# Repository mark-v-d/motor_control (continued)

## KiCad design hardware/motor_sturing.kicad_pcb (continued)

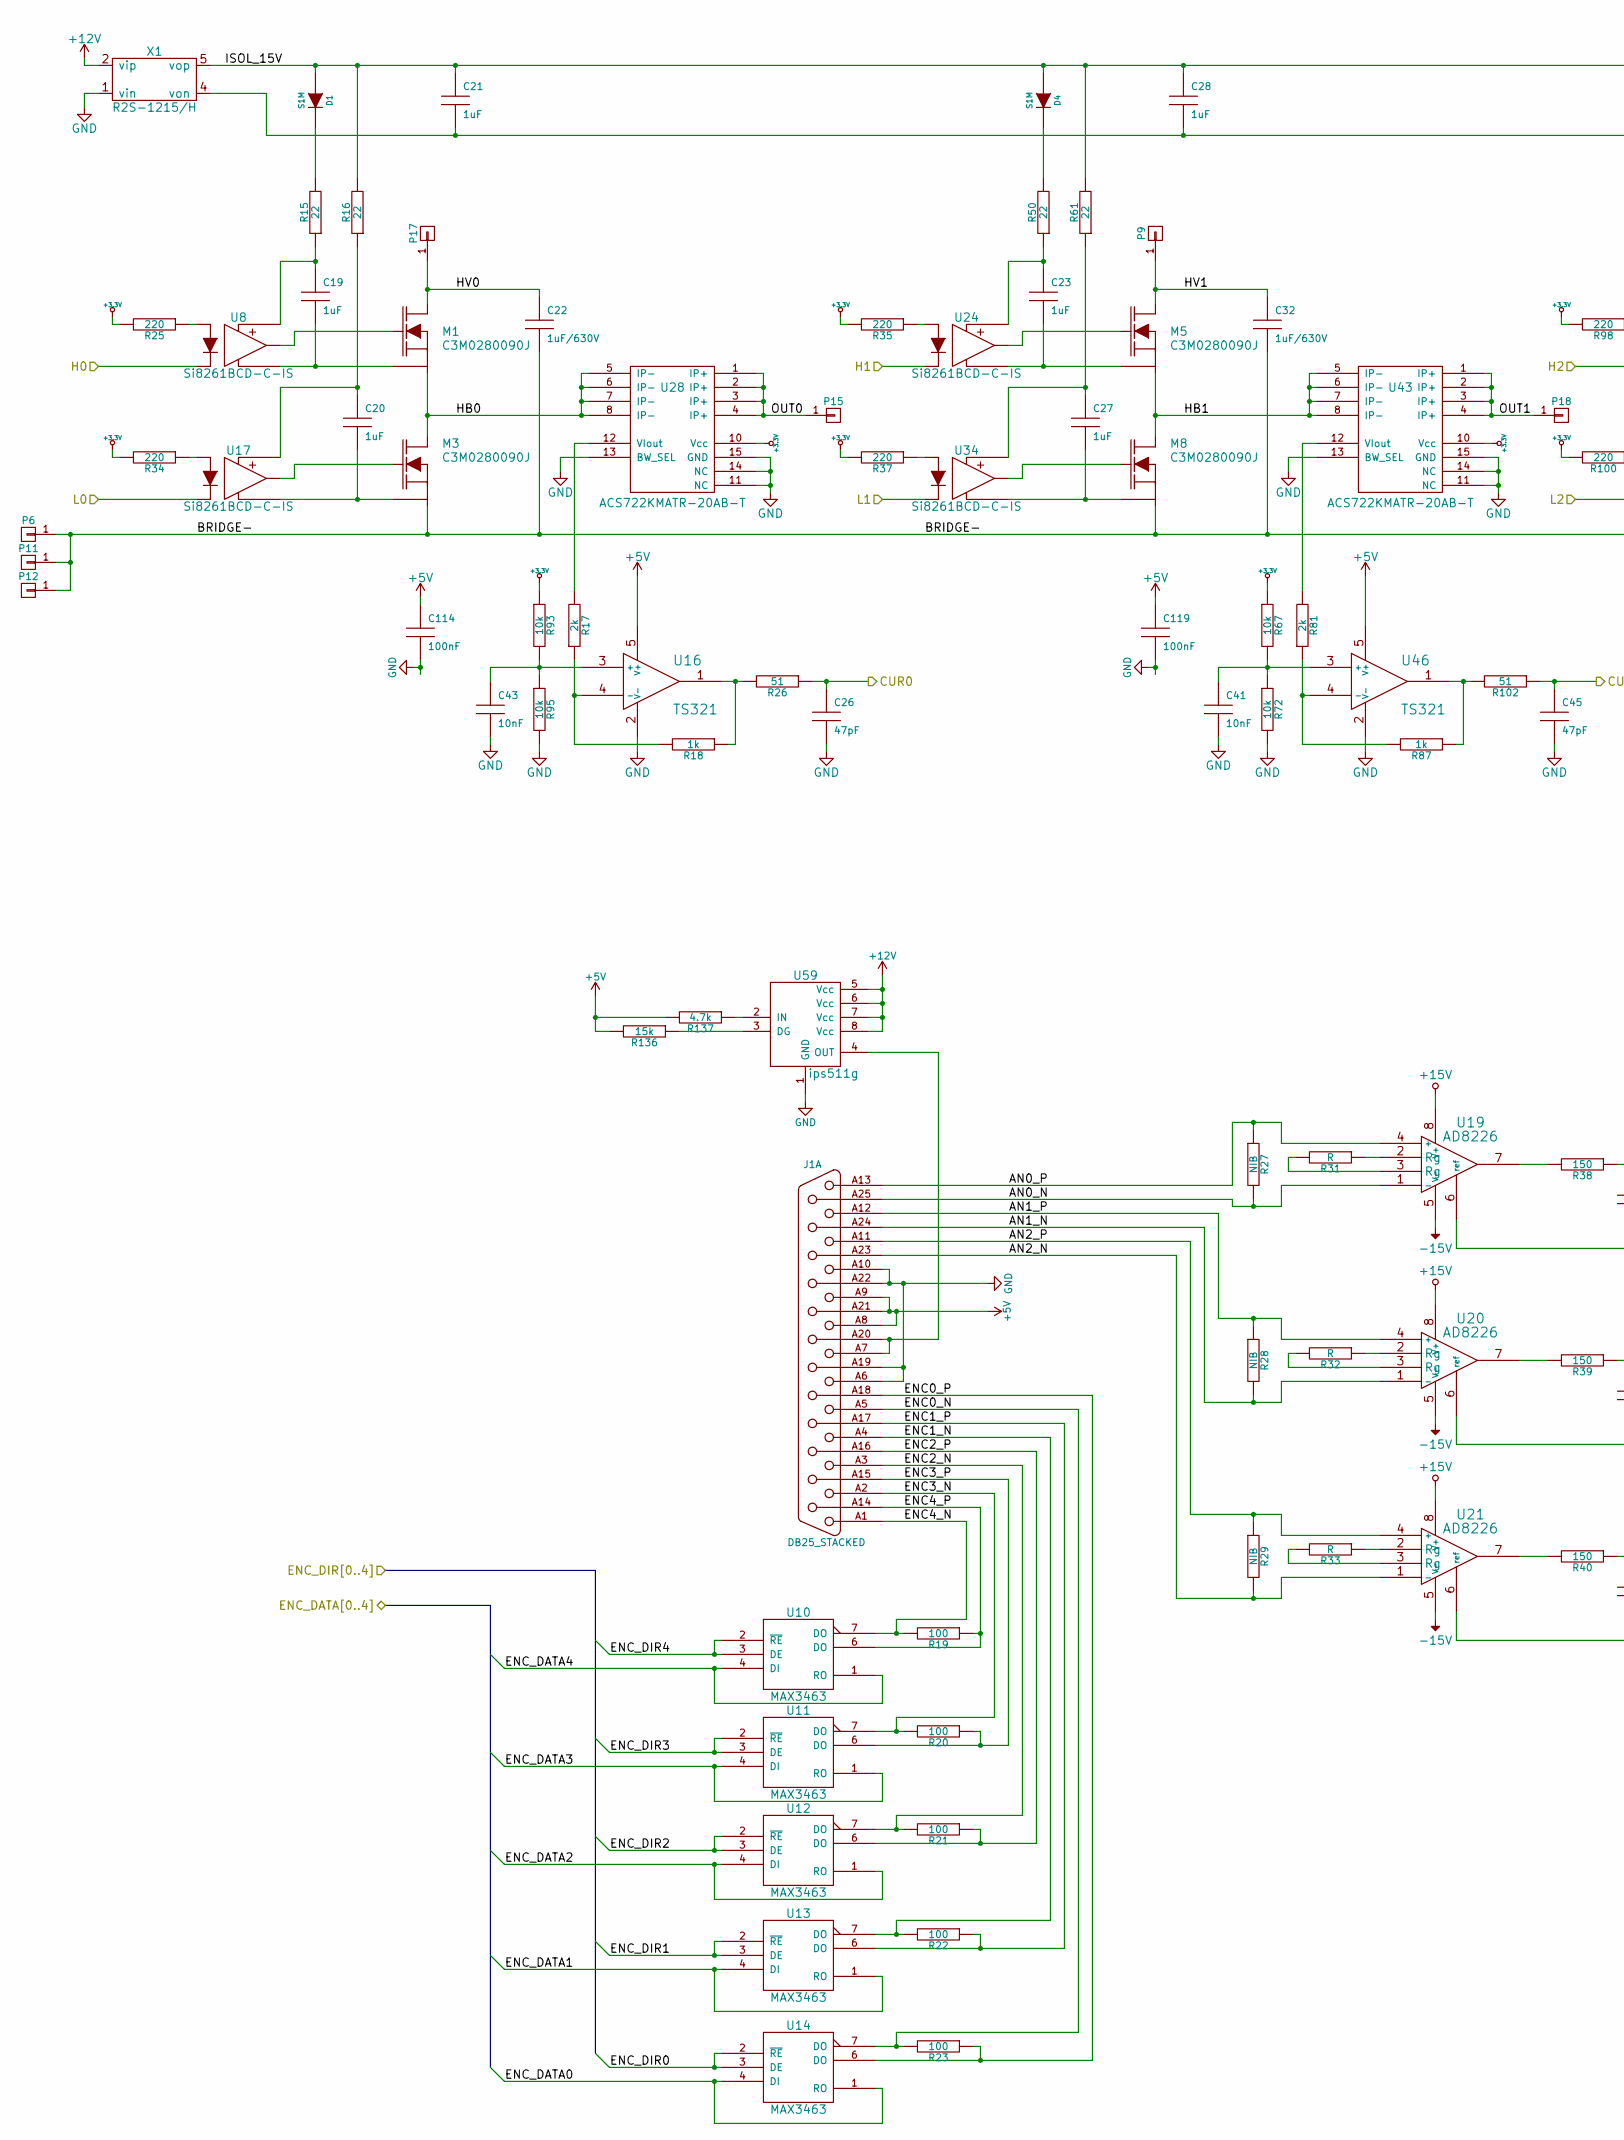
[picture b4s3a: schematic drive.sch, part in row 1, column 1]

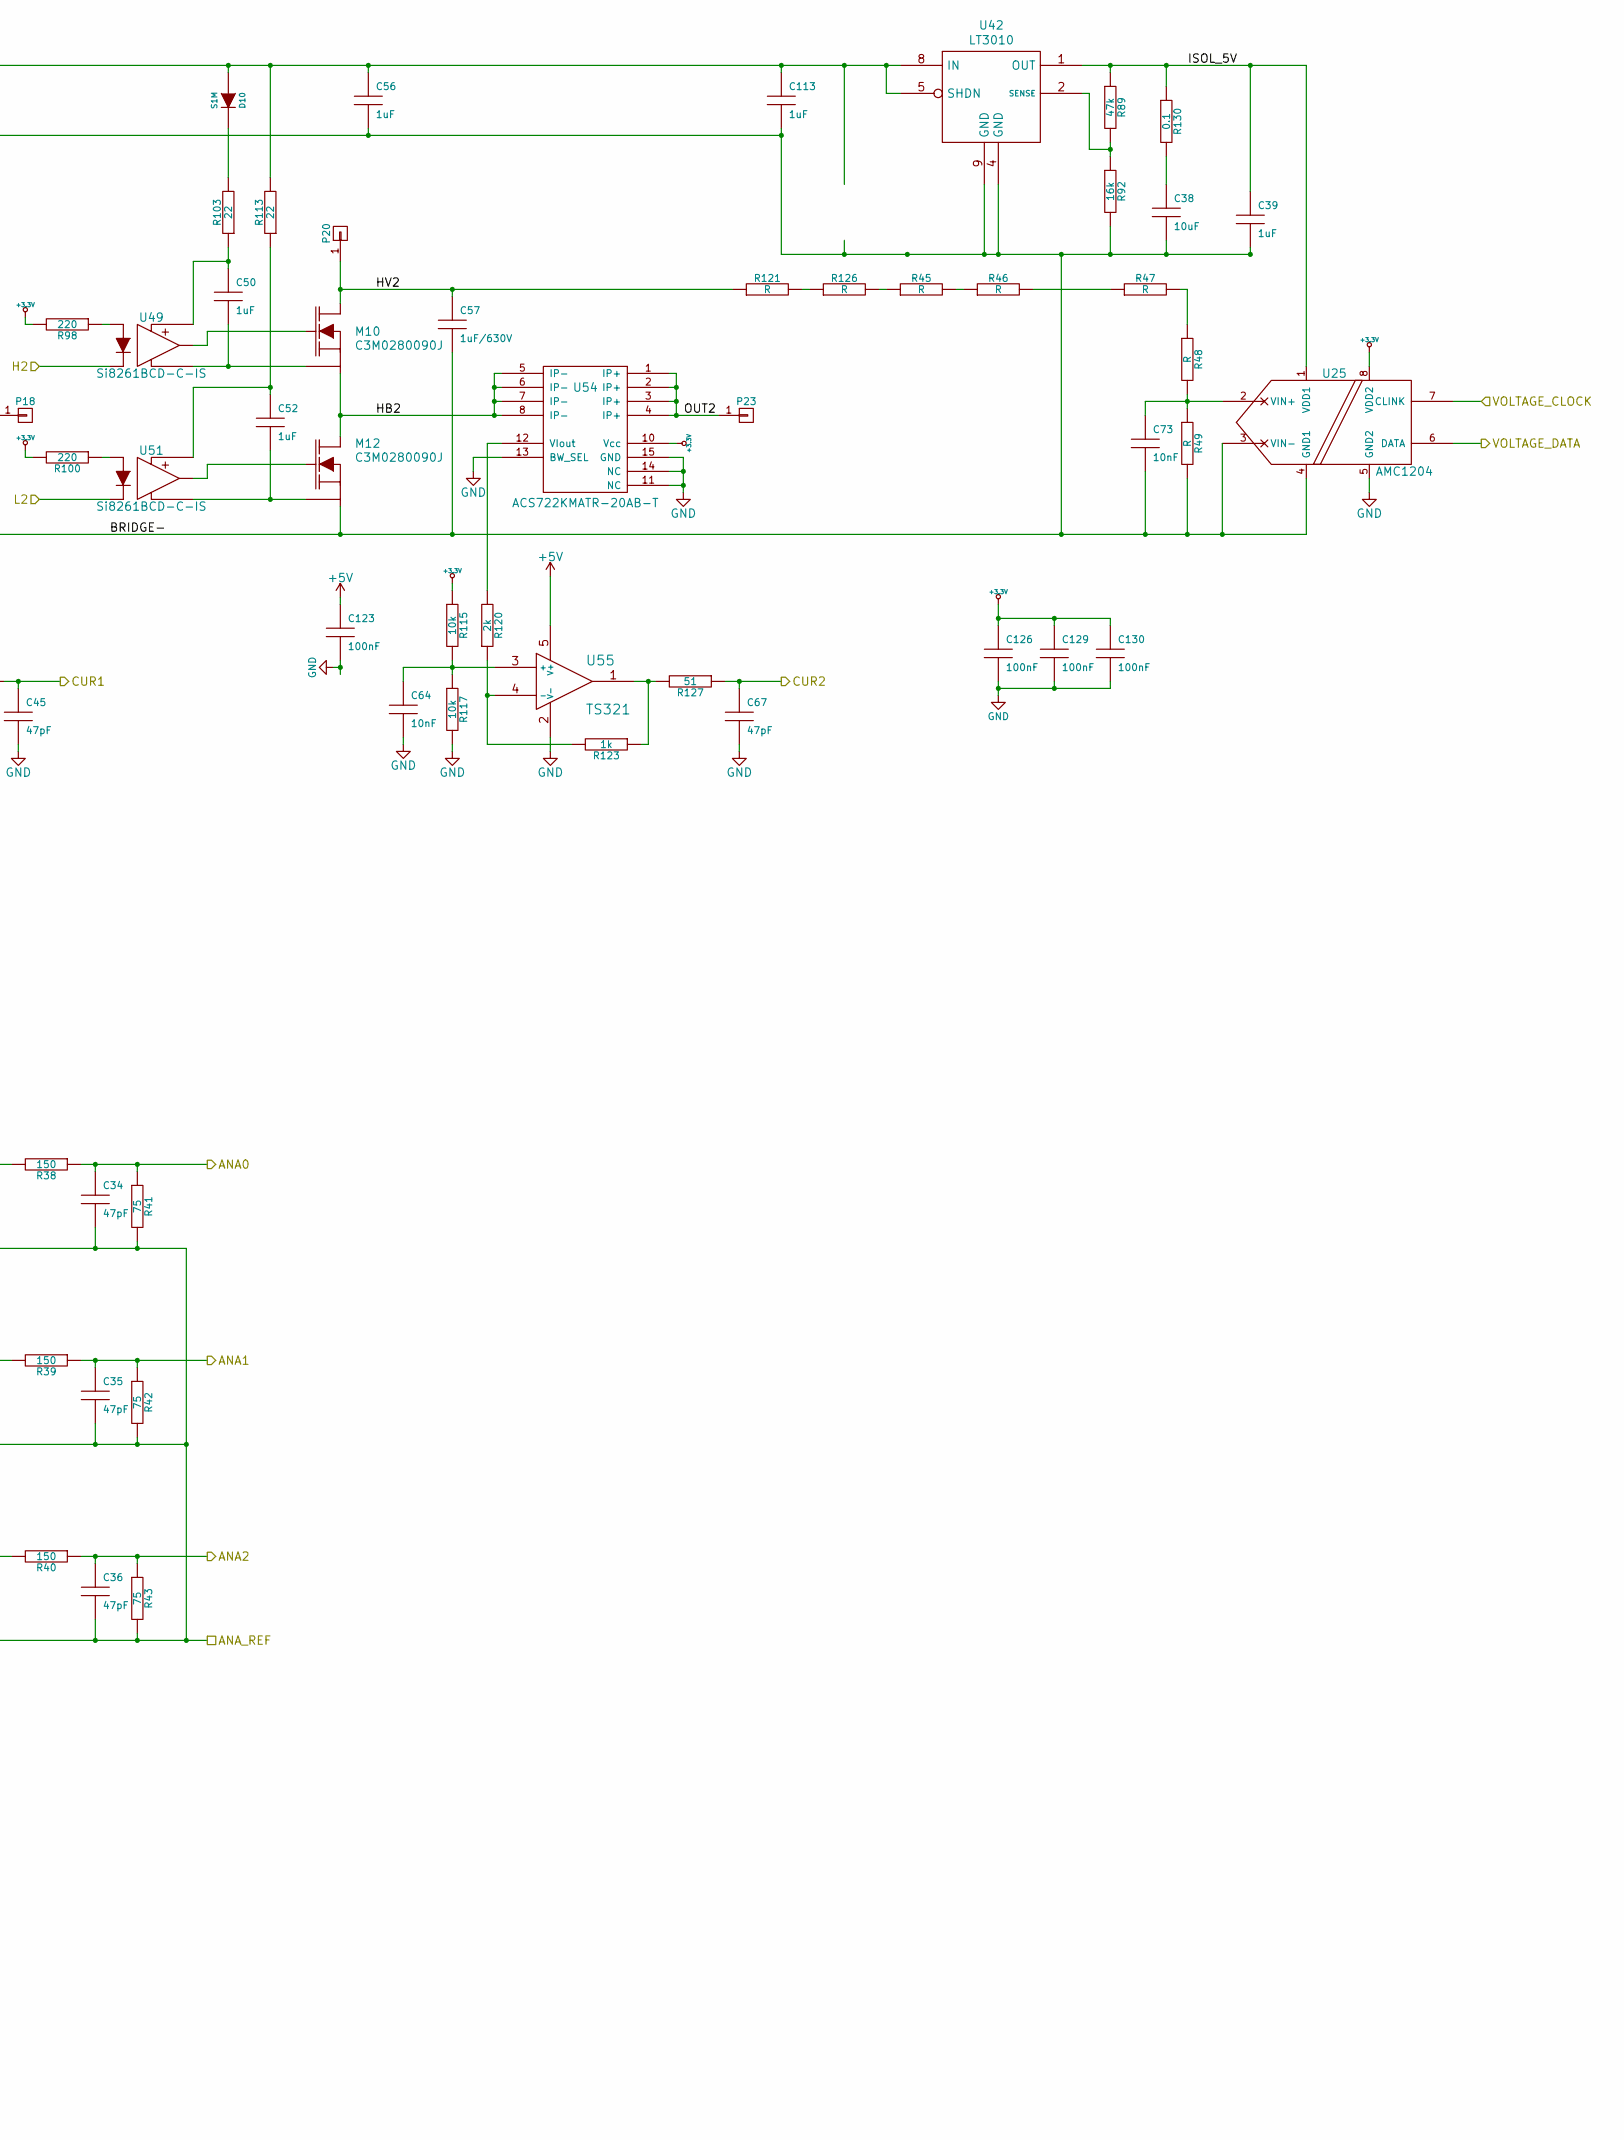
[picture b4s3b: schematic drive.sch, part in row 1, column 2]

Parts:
C19, C20, C21, C23, C27, C28, C39, C50, C52, C56, C113: 1uF; C0805
C22, C32, C57: 1uF/630V; C_2220
C26, C34, C35, C36, C45, C67: 47pF; C0603
C41, C43, C64, C73: 10nF; C0603
C65: 10uF; C1210
C115, C119, C123, C127, C129, C130: 100nF; C0603
D1, D4, D10: S1M; DO-214AC(SMA); Farnell 1858603
J1: DB25_STACKED; DB25FF_STACKED
M1, M3, M5, M8, M10, M12: C3M0280090J; TO-263-7-GDSKS; Mouser 941-C3M0280090J
P6: CONN_01X01; WE_9774080151R; Farnell 2497613
P9, P11, P12, P15, P17, P18, P20, P23: CONN_01X01; WE_9774080151R
R15, R16, R50, R61, R103, R113: 22; R0603
R17, R81, R120: 2k; R0603
R18, R87, R123: 1k; R0603
R19, R20, R21, R22, R23: 100; R0603
R25, R34, R35, R37, R98, R100: 220; R0603
R26, R102, R127: 51; R0603
R27, R28, R29: NIB; C0603
R31, R32, R33, R45, R46, R47, R48, R49, R121, R126: R; R0603
R38, R39, R40: 150; R0603
R41, R42, R43: 75; R0603
R67, R72, R93, R95, R115, R117: 10k; R0603
R89: 47k; R0603
R92: 16k; R0603
R129: 0.1; R0603
R135: 15k; R0603
R138: 4.7k; R0603
U8, U17, U24, U34, U49, U51: Si8261BCD-C-IS; SOIC-6_6.8x4.6mm_Pitch1.27mm; PartNr SI8261BCD-C-IS; Digikey 336-2418-5-ND
U9, U43, U54: ACS722KMATR-20AB-T; SOIC-16_7.5x10.3mm_Pitch1.27mm; PartNr ACS722KMATR-20AB; Digikey 620-1739-1-ND
U10, U11, U12, U13, U14: MAX3463; SOIC-8_3.9x4.9mm_Pitch1.27mm
U16, U46, U55: TS321; SOT23_5; PartNr TS321AILT; Farnell 1750165
U19, U20, U21: AD8226; SOIC-8_3.9x4.9mm_Pitch1.27mm; Farnell 1827360
U25: AMC1204; SO8_11; Digikey 296-37186-1-ND
U42: LT3010; MSOP-8-1EP_3x3mm_Pitch0.65mm; PartNr LT3010EMS8E#PBF; Farnell 1273635
U58: ips511g; SOIC-8_3.9x4.9mm_Pitch1.27mm
X1: R2S-1215/H; RECOM_R2S; Digikey R2S-1215/H-ND

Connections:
+3.3V: C127.1, C129.1, C130.1, R25.2, R34.2, R35.2, R37.2, R67.1, R93.1, R98.2, R100.2, R115.1, U9.10 (Vcc), U10.8 (+3.3V), U11.8 (+3.3V), U12.8 (+3.3V), U13.8 (+3.3V), U14.8 (+3.3V), U25.8 (VDD2), U43.10 (Vcc), U54.10 (Vcc); also elsewhere on the board
+5V: C115.1, C119.1, C123.1, J1.A8 (8), J1.A9 (9), J1.A21 (21), J1.B8 (8), J1.B9 (9), J1.B21 (21), R135.2, R138.2, U16.5 (V+), U46.5 (V+), U55.5 (V+); also elsewhere on the board
+12V: U58.5 (Vcc), U58.6 (Vcc), U58.7 (Vcc), U58.8 (Vcc), X1.2 (vip); also elsewhere on the board
+15V: U19.8 (V+), U20.8 (V+), U21.8 (V+); also elsewhere on the board
-15V: U19.5 (V-), U20.5 (V-), U21.5 (V-); also elsewhere on the board
/Drive_1/AN0_N: J1.A25 (P25), R27.2, U19.1 (-)
/Drive_1/AN0_P: J1.A13 (13), R27.1, U19.4 (+)
/Drive_1/AN1_N: J1.A24, R28.2, U20.1 (-)
/Drive_1/AN1_P: J1.A12 (12), R28.1, U20.4 (+)
/Drive_1/AN2_N: J1.A23 (P23), R29.2, U21.1 (-)
/Drive_1/AN2_P: J1.A11 (11), R29.1, U21.4 (+)
/Drive_1/ANA0: C34.1, R38.1, R41.1; also elsewhere on the board
/Drive_1/ANA1: C35.1, R39.1, R42.1; also elsewhere on the board
/Drive_1/ANA2: C36.1, R40.1, R43.1; also elsewhere on the board
/Drive_1/ANA_REF: C34.2, C35.2, C36.2, R41.2, R42.2, R43.2, U19.6 (ref), U20.6 (ref), U21.6 (ref); also elsewhere on the board
/Drive_1/CUR0: C26.1, R26.1; also elsewhere on the board
/Drive_1/CUR1: C45.1, R102.1; also elsewhere on the board
/Drive_1/CUR2: C67.1, R127.1; also elsewhere on the board
/Drive_1/ENC0_N: J1.A5 (5), R23.2, U14.7 (DO)
/Drive_1/ENC0_P: J1.A18 (P18), R23.1, U14.6 (DO)
/Drive_1/ENC1_N: J1.A4 (4), R22.2, U13.7 (DO)
/Drive_1/ENC1_P: J1.A17 (17), R22.1, U13.6 (DO)
/Drive_1/ENC2_N: J1.A3 (3), R21.2, U12.7 (DO)
/Drive_1/ENC2_P: J1.A16, R21.1, U12.6 (DO)
/Drive_1/ENC3_N: J1.A2, R20.2, U11.7 (DO)
/Drive_1/ENC3_P: J1.A15 (P15), R20.1, U11.6 (DO)
/Drive_1/ENC4_N: J1.A1 (1), R19.2, U10.7 (DO)
/Drive_1/ENC4_P: J1.A14 (P14), R19.1, U10.6 (DO)
/Drive_1/ENC_DATA0: U14.1 (RO), U14.4 (DI); also elsewhere on the board
/Drive_1/ENC_DATA1: U13.1 (RO), U13.4 (DI); also elsewhere on the board
/Drive_1/ENC_DATA2: U12.1 (RO), U12.4 (DI); also elsewhere on the board
/Drive_1/ENC_DATA3: U11.1 (RO), U11.4 (DI); also elsewhere on the board
/Drive_1/ENC_DATA4: U10.1 (RO), U10.4 (DI); also elsewhere on the board
/Drive_1/ENC_DIR0: U14.2 (~RE), U14.3 (DE); also elsewhere on the board
/Drive_1/ENC_DIR1: U13.2 (~RE), U13.3 (DE); also elsewhere on the board
/Drive_1/ENC_DIR2: U12.2 (~RE), U12.3 (DE); also elsewhere on the board
/Drive_1/ENC_DIR3: U11.2 (~RE), U11.3 (DE); also elsewhere on the board
/Drive_1/ENC_DIR4: U10.2 (~RE), U10.3 (DE); also elsewhere on the board
/Drive_1/H0: U8.3 (cathode); also elsewhere on the board
/Drive_1/H1: U24.3 (cathode); also elsewhere on the board
/Drive_1/H2: U49.3 (cathode); also elsewhere on the board
/Drive_1/HB1: M5.S, M8.D, U43.5 (IP-), U43.6 (IP-), U43.7 (IP-), U43.8 (IP-)
/Drive_1/HB2: M10.S, M12.D, U54.5 (IP-), U54.6 (IP-), U54.7 (IP-), U54.8 (IP-)
/Drive_1/HV0: C22.1, M1.D, P17.1
/Drive_1/HV1: C32.1, M5.D, P9.1
/Drive_1/HV2: C57.1, M10.D, P20.1, R121.1
/Drive_1/ISOL_15V: C21.1, C28.1, C56.1, C113.1, D1.A, D4.A, D10.A, R16.2, R61.2, R113.2, U42.5 (SHDN), U42.8 (IN), X1.5 (vop)
/Drive_1/OUT1: P18.1, U43.1 (IP+), U43.2 (IP+), U43.3 (IP+), U43.4 (IP+)
/Drive_1/OUT2: P23.1, U54.1 (IP+), U54.2 (IP+), U54.3 (IP+), U54.4 (IP+)
/Drive_1/VOLTAGE_CLOCK: U25.7 (CLINK); also elsewhere on the board
/Drive_2/AN0_N: J1.B25 (P25); also elsewhere on the board
/Drive_2/AN0_P: J1.B13 (13); also elsewhere on the board
/Drive_2/AN1_N: J1.B24 (A24); also elsewhere on the board
/Drive_2/AN1_P: J1.B12 (12); also elsewhere on the board
/Drive_2/AN2_N: J1.B23 (P23); also elsewhere on the board
/Drive_2/AN2_P: J1.B11 (11); also elsewhere on the board
/Drive_2/ENC0_N: J1.B5 (5); also elsewhere on the board
/Drive_2/ENC0_P: J1.B18 (P18); also elsewhere on the board
/Drive_2/ENC1_N: J1.B4 (4); also elsewhere on the board
/Drive_2/ENC1_P: J1.B17 (17); also elsewhere on the board
/Drive_2/ENC2_N: J1.B3 (3); also elsewhere on the board
/Drive_2/ENC2_P: J1.B16 (A16); also elsewhere on the board
/Drive_2/ENC3_N: J1.B2 (A2); also elsewhere on the board
/Drive_2/ENC3_P: J1.B15 (P15); also elsewhere on the board
/Drive_2/ENC4_N: J1.B1 (1); also elsewhere on the board
/Drive_2/ENC4_P: J1.B14 (P14); also elsewhere on the board
/FPGA/HB_L0: U17.3 (cathode); also elsewhere on the board
/FPGA/HB_L1: U34.3 (cathode); also elsewhere on the board
/FPGA/HB_L2: U51.3 (cathode); also elsewhere on the board
/FPGA/VOLTAGE_D0: U25.6 (DATA); also elsewhere on the board
GND: C26.2, C41.2, C43.2, C45.2, C64.2, C67.2, C115.2, C119.2, C123.2, C127.2, C129.2, C130.2, J1.A6 (6), J1.A10 (10), J1.A19 (P19), J1.A22 (P22), J1.B6 (6), J1.B10 (10), J1.B19 (P19), J1.B22 (P22), R72.2, R95.2, R117.2, U9.11 (NC), U9.13 (BW_SEL), U9.14 (NC), U9.15 (GND), U10.5 (GND), U11.5 (GND), U12.5 (GND), U13.5 (GND), U14.5 (GND), U16.2 (V-), U25.5 (GND2), U43.11 (NC), U43.13 (BW_SEL), U43.14 (NC), U43.15 (GND), U46.2 (V-), U54.11 (NC), U54.13 (BW_SEL), U54.14 (NC), U54.15 (GND), U55.2 (V-), U58.1 (GND), X1.1 (vin); also elsewhere on the board
unnamed: C19.1, R15.1, U8.6 (vcc)
unnamed: C19.2, M1.KS (ks), U8.4 (gnd)
unnamed: C20.1, R16.1, U17.6 (vcc)
unnamed: C20.2, M3.KS (ks), U17.4 (gnd)
unnamed: C23.1, R50.1, U24.6 (vcc)
unnamed: C23.2, M5.KS (ks), U24.4 (gnd)
unnamed: C27.1, R61.1, U34.6 (vcc)
unnamed: C27.2, M8.KS (ks), U34.4 (gnd)
unnamed: C41.1, R67.2, R72.1, U46.3 (+)
unnamed: C43.1, R93.2, R95.1, U16.3 (+)
unnamed: C50.1, R103.1, U49.6 (vcc)
unnamed: C50.2, M10.KS (ks), U49.4 (gnd)
unnamed: C52.1, R113.1, U51.6 (vcc)
unnamed: C52.2, M12.KS (ks), U51.4 (gnd)
unnamed: C64.1, R115.2, R117.1, U55.3 (+)
unnamed: C65.1, R129.2
unnamed: C73.1, R48.2, R49.1, U25.2 (VIN+)
unnamed: D1.C, R15.2
unnamed: D4.C, R50.2
unnamed: D10.C, R103.2
unnamed: M1.G, U8.5 (out)
unnamed: M3.G, U17.5 (out)
unnamed: M5.G, U24.5 (out)
unnamed: M8.G, U34.5 (out)
unnamed: M10.G, U49.5 (out)
unnamed: M12.G, U51.5 (out)
unnamed: R17.1, R18.2, U16.4 (-)
unnamed: R18.1, R26.2, U16.1
unnamed: R25.1, U8.1 (anode)
unnamed: R31.1, U19.2 (Rg)
unnamed: R31.2, U19.3 (Rg)
unnamed: R32.1, U20.2 (Rg)
unnamed: R32.2, U20.3 (Rg)
unnamed: R33.1, U21.2 (Rg)
unnamed: R33.2, U21.3 (Rg)
unnamed: R34.1, U17.1 (anode)
unnamed: R35.1, U24.1 (anode)
unnamed: R37.1, U34.1 (anode)
unnamed: R38.2, U19.7
unnamed: R39.2, U20.7
unnamed: R40.2, U21.7
unnamed: R45.2, R46.1
unnamed: R46.2, R47.1
unnamed: R47.2, R48.1
unnamed: R81.1, R87.2, U46.4 (-)
unnamed: R81.2, U43.12 (VIout)
unnamed: R89.2, R92.1, U42.2 (SENSE)
unnamed: R98.1, U49.1 (anode)
unnamed: R100.1, U51.1 (anode)
unnamed: R87.1, R102.2, U46.1
unnamed: R120.1, R123.2, U55.4 (-)
unnamed: R120.2, U54.12 (VIout)
unnamed: R121.2, R126.1
unnamed: R123.1, R127.2, U55.1
unnamed: R45.1, R126.2
unnamed: R135.1, U58.3 (DG)
unnamed: R138.1, U58.2 (IN)

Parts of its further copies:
C24, C25, C29, C46, C47, C48, C51, C54, C55, C66, C112: 1uF; C0805
C30, C49, C58: 1uF/630V; C_2220
C37, C42, C59, C74: 10nF; C0603
C38: 10uF; C1210
C44, C53, C61, C62, C63, C68: 47pF; C0603
C114, C118, C122, C126, C128, C131: 100nF; C0603
D3, D7, D9: S1M; DO-214AC(SMA); Farnell 1858603
M2, M4, M6, M7, M9, M11: C3M0280090J; TO-263-7-GDSKS; Mouser 941-C3M0280090J
P7: CONN_01X01; WE_9774080151R; Farnell 2497613
P8, P10, P13, P14, P16, P19, P21, P22: CONN_01X01; WE_9774080151R
R24, R30, R36, R44, R97, R99: 220; R0603
R51, R52, R53, R62, R104, R114: 22; R0603
R54, R74, R119: 2k; R0603
R55, R88, R124: 1k; R0603
R56, R57, R58, R59, R60: 100; R0603
R63, R101, R128: 51; R0603
R64, R65, R66: NIB; C0603
R68, R69, R70, R82, R83, R84, R85, R86, R122, R125: R; R0603
R71, R73, R94, R96, R116, R118: 10k; R0603
R75, R76, R77: 150; R0603
R78, R79, R80: 75; R0603
R90: 47k; R0603
R91: 16k; R0603
R130: 0.1; R0603
R136: 15k; R0603
R137: 4.7k; R0603
U15, U18, U27, U35, U48, U52: Si8261BCD-C-IS; SOIC-6_6.8x4.6mm_Pitch1.27mm; PartNr SI8261BCD-C-IS; Digikey 336-2418-5-ND
U23: LT3010; MSOP-8-1EP_3x3mm_Pitch0.65mm; PartNr LT3010EMS8E#PBF; Farnell 1273635
U28, U36, U53: ACS722KMATR-20AB-T; SOIC-16_7.5x10.3mm_Pitch1.27mm; PartNr ACS722KMATR-20AB; Digikey 620-1739-1-ND
U29, U30, U31, U32, U33: MAX3463; SOIC-8_3.9x4.9mm_Pitch1.27mm
U37, U47, U56: TS321; SOT23_5; PartNr TS321AILT; Farnell 1750165
U38, U39, U40: AD8226; SOIC-8_3.9x4.9mm_Pitch1.27mm; Farnell 1827360
U44: AMC1204; SO8_11; Digikey 296-37186-1-ND
U59: ips511g; SOIC-8_3.9x4.9mm_Pitch1.27mm
X2: R2S-1215/H; RECOM_R2S; Digikey R2S-1215/H-ND

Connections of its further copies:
+3.3V: C126.1, C128.1, C131.1, R24.2, R30.2, R36.2, R44.2, R71.1, R94.1, R97.2, R99.2, R116.1, U28.10 (Vcc), U29.8 (+3.3V), U30.8 (+3.3V), U31.8 (+3.3V), U32.8 (+3.3V), U33.8 (+3.3V), U36.10 (Vcc), U44.8 (VDD2), U53.10 (Vcc); also elsewhere on the board
+5V: C114.1, C118.1, C122.1, R136.2, R137.2, U37.5 (V+), U47.5 (V+), U56.5 (V+); also elsewhere on the board
+12V: U59.5 (Vcc), U59.6 (Vcc), U59.7 (Vcc), U59.8 (Vcc), X2.2 (vip); also elsewhere on the board
+15V: U38.8 (V+), U39.8 (V+), U40.8 (V+); also elsewhere on the board
-15V: U38.5 (V-), U39.5 (V-), U40.5 (V-); also elsewhere on the board
/Drive_1/ANA_REF: C61.2, C62.2, C63.2, R78.2, R79.2, R80.2, U38.6 (ref), U39.6 (ref), U40.6 (ref); also elsewhere on the board
/Drive_1/VOLTAGE_CLOCK: U44.7 (CLINK); also elsewhere on the board
/Drive_2/AN0_N: R64.2, U38.1 (-); also elsewhere on the board
/Drive_2/AN0_P: R64.1, U38.4 (+); also elsewhere on the board
/Drive_2/AN1_N: R65.2, U39.1 (-); also elsewhere on the board
/Drive_2/AN1_P: R65.1, U39.4 (+); also elsewhere on the board
/Drive_2/AN2_N: R66.2, U40.1 (-); also elsewhere on the board
/Drive_2/AN2_P: R66.1, U40.4 (+); also elsewhere on the board
/Drive_2/ANA0: C61.1, R75.1, R78.1; also elsewhere on the board
/Drive_2/ANA1: C62.1, R76.1, R79.1; also elsewhere on the board
/Drive_2/ANA2: C63.1, R77.1, R80.1; also elsewhere on the board
/Drive_2/CUR0: C53.1, R63.1; also elsewhere on the board
/Drive_2/CUR1: C44.1, R101.1; also elsewhere on the board
/Drive_2/CUR2: C68.1, R128.1; also elsewhere on the board
/Drive_2/ENC0_N: R60.2, U33.7 (DO); also elsewhere on the board
/Drive_2/ENC0_P: R60.1, U33.6 (DO); also elsewhere on the board
/Drive_2/ENC1_N: R59.2, U32.7 (DO); also elsewhere on the board
/Drive_2/ENC1_P: R59.1, U32.6 (DO); also elsewhere on the board
/Drive_2/ENC2_N: R58.2, U31.7 (DO); also elsewhere on the board
/Drive_2/ENC2_P: R58.1, U31.6 (DO); also elsewhere on the board
/Drive_2/ENC3_N: R57.2, U30.7 (DO); also elsewhere on the board
/Drive_2/ENC3_P: R57.1, U30.6 (DO); also elsewhere on the board
/Drive_2/ENC4_N: R56.2, U29.7 (DO); also elsewhere on the board
/Drive_2/ENC4_P: R56.1, U29.6 (DO); also elsewhere on the board
/Drive_2/ENC_DATA0: U33.1 (RO), U33.4 (DI); also elsewhere on the board
/Drive_2/ENC_DATA1: U32.1 (RO), U32.4 (DI); also elsewhere on the board
/Drive_2/ENC_DATA2: U31.1 (RO), U31.4 (DI); also elsewhere on the board
/Drive_2/ENC_DATA3: U30.1 (RO), U30.4 (DI); also elsewhere on the board
/Drive_2/ENC_DATA4: U29.1 (RO), U29.4 (DI); also elsewhere on the board
/Drive_2/ENC_DIR0: U33.2 (~RE), U33.3 (DE); also elsewhere on the board
/Drive_2/ENC_DIR1: U32.2 (~RE), U32.3 (DE); also elsewhere on the board
/Drive_2/ENC_DIR2: U31.2 (~RE), U31.3 (DE); also elsewhere on the board
/Drive_2/ENC_DIR3: U30.2 (~RE), U30.3 (DE); also elsewhere on the board
/Drive_2/ENC_DIR4: U29.2 (~RE), U29.3 (DE); also elsewhere on the board
/Drive_2/H0: U15.3 (cathode); also elsewhere on the board
/Drive_2/H1: U27.3 (cathode); also elsewhere on the board
/Drive_2/H2: U48.3 (cathode); also elsewhere on the board
/Drive_2/HB1: M6.S, M7.D, U36.5 (IP-), U36.6 (IP-), U36.7 (IP-), U36.8 (IP-)
/Drive_2/HB2: M9.S, M11.D, U53.5 (IP-), U53.6 (IP-), U53.7 (IP-), U53.8 (IP-)
/Drive_2/HV0: C49.1, M2.D, P16.1
/Drive_2/HV1: C30.1, M6.D, P10.1
/Drive_2/HV2: C58.1, M9.D, P21.1, R122.1
/Drive_2/ISOL_15V: C29.1, C48.1, C55.1, C112.1, D3.A, D7.A, D9.A, R53.2, R62.2, R114.2, U23.5 (SHDN), U23.8 (IN), X2.5 (vop)
/Drive_2/OUT1: P19.1, U36.1 (IP+), U36.2 (IP+), U36.3 (IP+), U36.4 (IP+)
/Drive_2/OUT2: P22.1, U53.1 (IP+), U53.2 (IP+), U53.3 (IP+), U53.4 (IP+)
/FPGA/HB_L3: U18.3 (cathode); also elsewhere on the board
/FPGA/HB_L4: U35.3 (cathode); also elsewhere on the board
/FPGA/HB_L5: U52.3 (cathode); also elsewhere on the board
/FPGA/VOLTAGE_D1: U44.6 (DATA); also elsewhere on the board
GND: C37.2, C42.2, C44.2, C53.2, C59.2, C68.2, C114.2, C118.2, C122.2, C126.2, C128.2, C131.2, R73.2, R96.2, R118.2, U28.11 (NC), U28.13 (BW_SEL), U28.14 (NC), U28.15 (GND), U29.5 (GND), U30.5 (GND), U31.5 (GND), U32.5 (GND), U33.5 (GND), U36.11 (NC), U36.13 (BW_SEL), U36.14 (NC), U36.15 (GND), U37.2 (V-), U44.5 (GND2), U47.2 (V-), U53.11 (NC), U53.13 (BW_SEL), U53.14 (NC), U53.15 (GND), U56.2 (V-), U59.1 (GND), X2.1 (vin); also elsewhere on the board
unnamed: C24.1, R51.1, U27.6 (vcc)
unnamed: C24.2, M6.KS (ks), U27.4 (gnd)
unnamed: C25.1, R62.1, U35.6 (vcc)
unnamed: C25.2, M7.KS (ks), U35.4 (gnd)
unnamed: C37.1, R71.2, R73.1, U47.3 (+)
unnamed: C38.1, R130.2
unnamed: C42.1, R94.2, R96.1, U37.3 (+)
unnamed: C46.1, R52.1, U15.6 (vcc)
unnamed: C46.2, M2.KS (ks), U15.4 (gnd)
unnamed: C47.1, R53.1, U18.6 (vcc)
unnamed: C47.2, M4.KS (ks), U18.4 (gnd)
unnamed: C51.1, R104.1, U48.6 (vcc)
unnamed: C51.2, M9.KS (ks), U48.4 (gnd)
unnamed: C54.1, R114.1, U52.6 (vcc)
unnamed: C54.2, M11.KS (ks), U52.4 (gnd)
unnamed: C59.1, R116.2, R118.1, U56.3 (+)
unnamed: C74.1, R85.2, R86.1, U44.2 (VIN+)
unnamed: D3.C, R51.2
unnamed: D7.C, R52.2
unnamed: D9.C, R104.2
unnamed: M2.G, U15.5 (out)
unnamed: M4.G, U18.5 (out)
unnamed: M6.G, U27.5 (out)
unnamed: M7.G, U35.5 (out)
unnamed: M9.G, U48.5 (out)
unnamed: M11.G, U52.5 (out)
unnamed: R24.1, U15.1 (anode)
unnamed: R30.1, U18.1 (anode)
unnamed: R36.1, U27.1 (anode)
unnamed: R44.1, U35.1 (anode)
unnamed: R54.1, R55.2, U37.4 (-)
unnamed: R55.1, R63.2, U37.1
unnamed: R68.1, U38.2 (Rg)
unnamed: R68.2, U38.3 (Rg)
unnamed: R69.1, U39.2 (Rg)
unnamed: R69.2, U39.3 (Rg)
unnamed: R70.1, U40.2 (Rg)
unnamed: R70.2, U40.3 (Rg)
unnamed: R74.1, R88.2, U47.4 (-)
unnamed: R74.2, U36.12 (VIout)
unnamed: R75.2, U38.7
unnamed: R76.2, U39.7
unnamed: R77.2, U40.7
unnamed: R82.2, R83.1
unnamed: R83.2, R84.1
unnamed: R84.2, R85.1
unnamed: R90.2, R91.1, U23.2 (SENSE)
unnamed: R97.1, U48.1 (anode)
unnamed: R99.1, U52.1 (anode)
unnamed: R88.1, R101.2, U47.1
unnamed: R119.1, R124.2, U56.4 (-)
unnamed: R119.2, U53.12 (VIout)
unnamed: R122.2, R125.1
unnamed: R124.1, R128.2, U56.1
unnamed: R82.1, R125.2
unnamed: R136.1, U59.3 (DG)
unnamed: R137.1, U59.2 (IN)

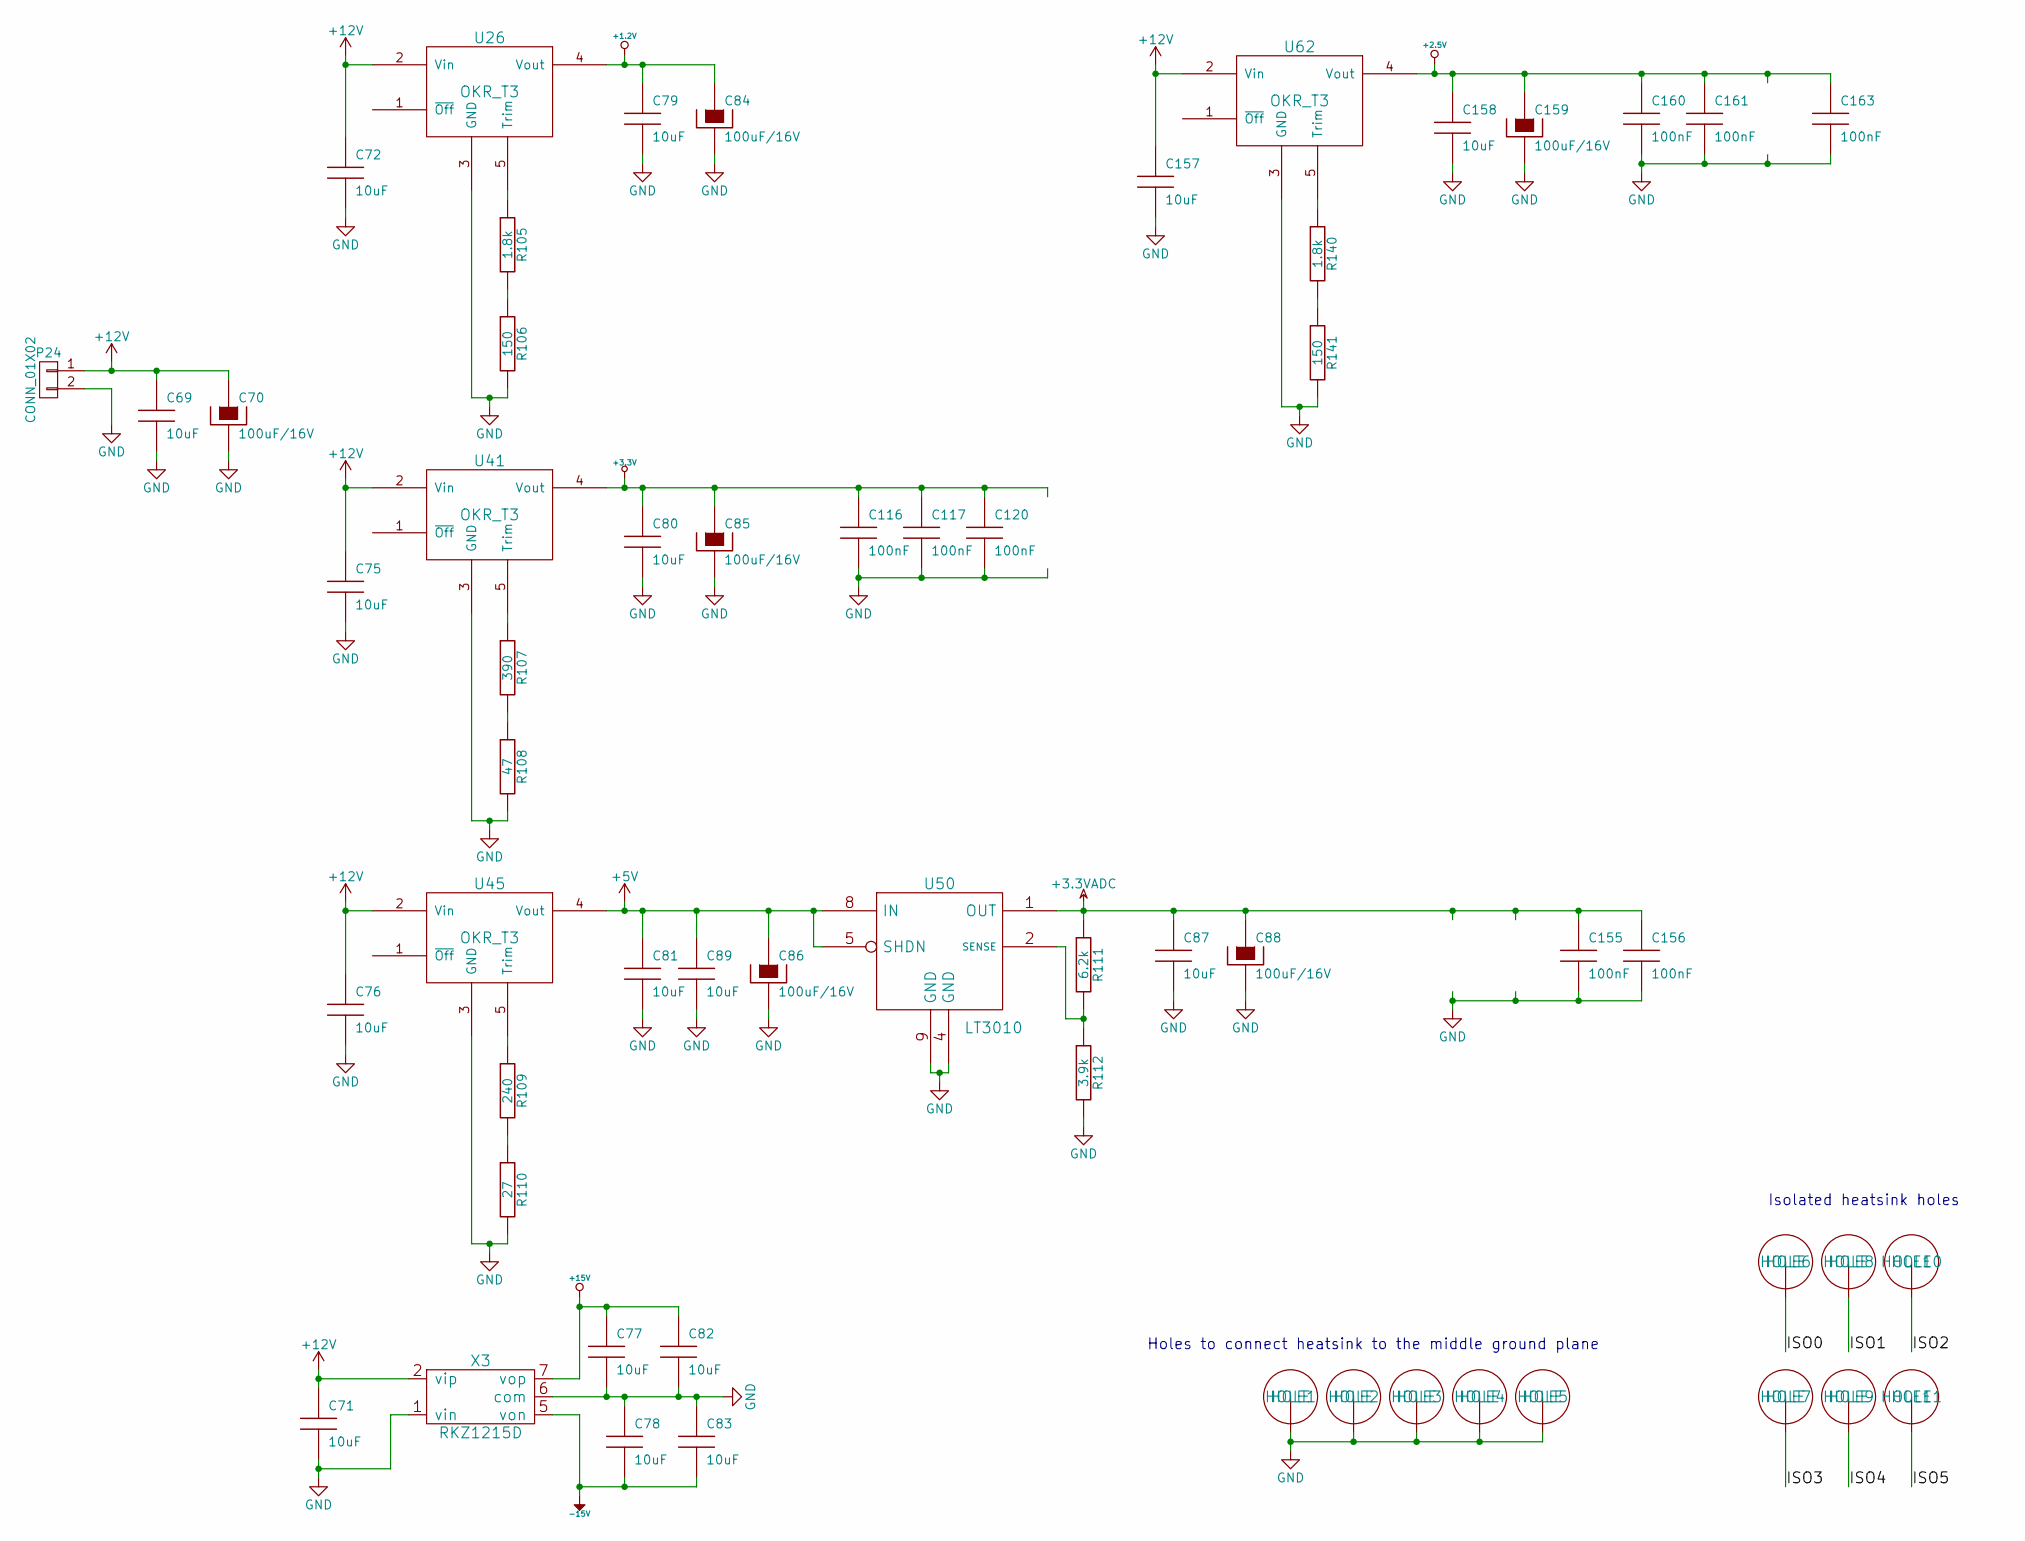
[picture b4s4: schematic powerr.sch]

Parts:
C69, C71, C72, C75, C76, C77, C78, C79, C80, C81, C82, C83, C87, C89, C157, C158: 10uF; C1210
C70, C84, C85, C86, C88, C159: 100uF/16V; c_elec_6.3x5.3
C116, C117, C120, C155, C156, C160, C161, C163: 100nF; C0603
HOLE1, HOLE2, HOLE3, HOLE4, HOLE5, HOLE6, HOLE7, HOLE8, HOLE9, HOLE10, HOLE11: HOLE; hole_3mm
P24: CONN_01X02; FCI_02_5mm; PartNr 20020109-G021A01LF; Farnell 1860166
R105, R140: 1.8k; R0603
R106, R141: 150; R0603
R107: 390; R0603
R108: 47; R0603
R109: 240; R0603
R110: 27; R0603
R111: 6.2k; R0603
R112: 3.9k; R0603
U26, U41, U45, U62: OKR_T3; okr_t3; PartNr OKR-T/3; Farnell 1736768
U50: LT3010; MSOP-8-1EP_3x3mm_Pitch0.65mm; PartNr LT3010EMS8E#PBF; Farnell 1273635
X3: RKZ1215D; RKZXXXXD

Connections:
+1.2V: C79.1, C84.1, U26.4 (Vout); also elsewhere on the board
+2.5V: C158.1, C159.1, C160.1, C161.1, C163.1, U62.4 (Vout); also elsewhere on the board
+3.3V: C80.1, C85.1, C116.1, C117.1, C120.1, U41.4 (Vout); also elsewhere on the board
+3.3VADC: C87.1, C88.1, C155.1, C156.1, R111.1, U50.1 (OUT); also elsewhere on the board
+5V: C81.1, C86.1, C89.1, U45.4 (Vout), U50.5 (SHDN), U50.8 (IN); also elsewhere on the board
+12V: C69.1, C70.1, C71.1, C72.1, C75.1, C76.1, C157.1, P24.1, U26.2 (Vin), U41.2 (Vin), U45.2 (Vin), U62.2 (Vin), X3.2 (vip); also elsewhere on the board
+15V: C77.1, C82.1, X3.7 (vop); also elsewhere on the board
-15V: C78.2, C83.2, X3.5 (von); also elsewhere on the board
/Power/ISO0: HOLE6.1
/Power/ISO1: HOLE8.1
/Power/ISO2: HOLE10.1
/Power/ISO3: HOLE7.1
/Power/ISO4: HOLE9.1
/Power/ISO5: HOLE11.1
GND: C69.2, C70.2, C71.2, C72.2, C75.2, C76.2, C77.2, C78.1, C79.2, C80.2, C81.2, C82.2, C83.1, C84.2, C85.2, C86.2, C87.2, C88.2, C89.2, C116.2, C117.2, C120.2, C155.2, C156.2, C157.2, C158.2, C159.2, C160.2, C161.2, C163.2, HOLE1.1, HOLE2.1, HOLE3.1, HOLE4.1, HOLE5.1, P24.2, R106.2, R108.2, R110.2, R112.2, R141.2, U26.3 (GND), U41.3 (GND), U45.3 (GND), U50.4 (GND), U50.9 (GND), U62.3 (GND), X3.1 (vin), X3.6 (com); also elsewhere on the board
unnamed: R105.1, U26.5 (Trim)
unnamed: R105.2, R106.1
unnamed: R107.1, U41.5 (Trim)
unnamed: R107.2, R108.1
unnamed: R109.1, U45.5 (Trim)
unnamed: R109.2, R110.1
unnamed: R111.2, R112.1, U50.2 (SENSE)
unnamed: R140.1, U62.5 (Trim)
unnamed: R140.2, R141.1

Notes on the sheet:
Holes to connect heatsink to the middle ground plane
Isolated heatsink holes

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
